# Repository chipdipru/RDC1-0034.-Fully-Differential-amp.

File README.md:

<p><a href="https://www.chipdip.ru/product/fully-differential-amp.rdc1-0034">RDC1-0034</a> - полностью дифференциальный усилитель. Он обеспечивает высочайшее качество звука с очень низким уровнем шума. Операционный усилитель, рекомендуемый для установки в этот модуль - <a href="https://www.chipdip.ru/product/opa1632dgn" class="link">OPA1632</a>. Он работает в широком диапазоне частот вплоть до 180 МГц и имеет очень высокую скорость нарастания сигнала - 50 В/мкс. Всё это обеспечивает исключительно низкие искажения – 0,000023%.  А очень низкая спектральная плотность шума, всего 1,3 нВ / v Гц, обеспечивает максимальное отношение сигнал-шум и широкий динамический диапазон. Дифференциальные вход и выход уменьшают гармоники четного порядка и минимизирует шумовые помехи. </p><p><h2>Технические характеристики:</h2></p>
Полоса воспроизводимых частот (ограничена активным ФНЧ)  - 1.6Гц…80кГц<br>
Коэффициент нелинейных искажений THD + N @ 1 kHz - 0.000022%<br>
Коэффициент подавления синфазного сигнала – 90дБ<br>
Скорость нарастания выходного сигнала - 50В/мкс<br>
Спектральная плотность шума - 1,3нВ/vГц<br>
Выходной ток – 85мА<br>
Рекомендованное напряжение питания -  12В<br>
Возможное напряжение питания – 5…30В<p><p><h2>Схема</h2></p><p></p><p>На схеме отображены два корпуса микросхемы OPA1632. Для сборки выбирайте один MSOP-8 или SO-8. </p><p><h2>Монтажная схема</h2></p><p></p><p>Обратите внимание. На плате два посадочных. Одно на стороне расположения деталей предназначено для корпуса MSOP-8, а на тыльной стороне для корпуса SO-8.</p><p>Для использования модуля в качестве предварительного усилителя для наших усилителей класса D, рекомендуем запитывать его напряжением 12В. Напряжение питания 12В можно подать непосредственно на вход Vin установив перемычку R9. Если же вы будете использовать модуль совместно с нашими усилителями, то можно будет использовать дополнительный понижающий преобразователь RDC1-0013 12V, который обеспечит питание 12В из 15…48В.</p><p><h2>Схема подключения напряжения питания 12В.</h2></p><p></p><p><h2>Схема подключения напряжения питания 15…48В с помощью <a href="https://www.chipdip.ru/product/rdc1-0013-12v" class="link">RDC1-0013 12V</a></h2></p><p></p><p><h2>Схема подключения напряжения питания 15В с помощью LM7812</h2></p><p></p><p><h2>Не симметричный вход.</h2></p><p>При необходимости подать на вход не симметричный сигнал необходимо установить перемычку GND. </p><p><h2>Эксперимент </h2></p><p>Попробуйте поэкспериментировать: замените операционный усилитель OPA1632 менее дорогими <a href="https://www.chipdip.ru/product/ad8132ar" class="link">AD8132</a> или <a href="https://www.chipdip.ru/product/ad8138arz" class="link">AD8138</a>. Вы приятно удивитесь. Не забудьте, что питание модуля в этом случае не должно превышать Vin = 5В. Используйте <a href="https://www.chipdip.ru/product/rdc1-0013-5v" class="link">RDC1-0013 5V</a> для преобразования напряжения 15-48В или LM7805 для преобразования 15В.</p><p>Это открытый проект! Лицензия, под которой он распространяется – <a href="https://creativecommons.org/licenses/by-sa/3.0/" class="link">Creative Commons - Attribution - Share Alike license</a>.</p>

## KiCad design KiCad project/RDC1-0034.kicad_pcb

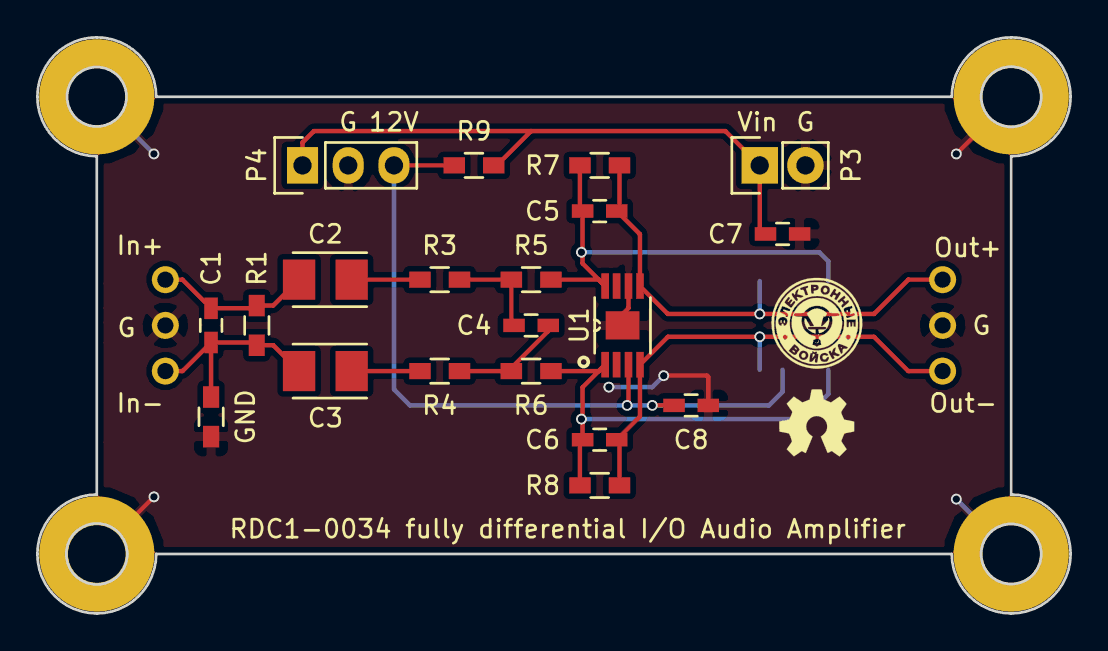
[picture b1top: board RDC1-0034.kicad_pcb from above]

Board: 2 copper layers, 57.4 x 32.0 mm, 23 parts (1 on the bottom side), 13 nets.

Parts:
C1: 1n; C_0603_HandSoldering
C2, C3: 10uF; TantalC_SizeB_EIA-3528_Reflow
C4: 470p; C_0603_HandSoldering
C5, C6: 150p; C_0603_HandSoldering
C7, C8: 0,1; C_0603_HandSoldering
GND: 0; R_0603_HandSoldering
P1, P2: CONN_01X03; Pin_Header_ring_1x03_mm
P3: CONN_01X02; Pin_Header_Straight_1x02
P4: CONN_01X03; Pin_Header_Straight_1x03
R1: 100k; R_0603_HandSoldering
R3, R4, R5, R6: 2k2; R_0603_HandSoldering
R7, R8: 20k; R_0603_HandSoldering
R9: 0; R_0603_HandSoldering
U1: OPA1632DGN; SOP65P490X110-9N
U2: OPA1632DR; SOIC127P600X175-8N

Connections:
12V: C8.1, P4.3, R9.1, U1.3, U2.3
GND: C7.1, C8.2, GND.1, P1.2, P2.2, P3.2, P4.2, U1.6, U1.9, U2.6
unnamed: C1.1, C2.2, P1.1, R1.2
unnamed: C1.2, C3.2, GND.2, P1.3, R1.1
unnamed: C2.1, R3.2
unnamed: C3.1, R4.2
unnamed: C4.1, R3.1, R5.2
unnamed: C4.2, R4.1, R6.2
unnamed: C5.1, P2.1, R7.1, U1.5, U2.5
unnamed: C5.2, R5.1, R7.2, U1.8, U2.8
unnamed: C6.1, P2.3, R8.1, U1.4, U2.4
unnamed: C6.2, R6.1, R8.2, U1.1, U2.1
unnamed: C7.2, P3.1, P4.1, R9.2

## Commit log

2018-09-26 KiCad project
2018-09-26 Gerber files
